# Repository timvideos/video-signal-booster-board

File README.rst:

Video Booster Board
===================

.. image:: ./img/vsb-board.png

Overview:
---------

This repository contains a KiCad PCB project for an open hardware board design that allows to improve the quality of HDMI video signals transmitted over long cables.

Key features:
-------------

* HDMI signal preconditioning with a pair of `PTN3363 <https://www.nxp.com/docs/en/data-sheet/PTN3363.pdf>`_ HDMI level shifters.
* Signal equalization controlled with on-board DIP-Switch
* On-board SiLabs `EFM32HG322F64 <https://www.silabs.com/documents/public/data-sheets/efm32hg-datasheet.pdf>`_ MCU for interactive control and board monitoring
* Supports different EDID connection scenarios

Mechanical layout and dimensions
--------------------------------

The board has been mechanically optimised for usage with the `Numato Opsis <https://hdmi2usb.tv/numato-opsis/>`_ open video capture device.
It is possible to use it with different platforms using HDMI extender cables.

.. image:: ./img/layout.png

It follows the data flow diagram presented below:

.. image:: ./img/vsb-data-flow.svg

Getting Started
---------------

Please refer to KiCad schematic files for more information regarding hardware functionalities implemented in the design.
The PCB layout has been defined with a 4-layer stackup.
Please check the geometry of differential traces implemented in the design with stackup offered by PCB vendor for optimal impedance match of HDMI traces.
There is a BOM document generated from the schematics and shared in this repository.
Please short the ``J5,J7,J8,J12`` solder jumpers on the bottom side of the PCB.
This will relay the EDID signals on both HDMI channels from input to output.
Short the ``J11,J4`` jumpers if you plan to experiment with the provided example MCU firmware.
This will make the on-board MCU accessible on EDID bus driven from ``J2`` HDMI input connector.
Please check the schematics and software codebase for any other jumper configuration.

Example firmware
----------------

The EFM32 MCU used in the design comes with a factory programmed ``AN0042`` bootloader.
In order to  make the MCU compatible with the provided example firmware it is advisable to replace the default bootloader with `Toboot <https://github.com/im-tomu/toboot>`_
over SWD interface using `OpenOCD <http://openocd.org/>`_.
The SWD signals from the MCU are exposed on test pads marked with ``IO`` and ``CLK`` on the bottom side of the Video Booster Board.
Additionally there are test pads with system ground and power supply exposed next to them.

To upload the ``Toboot`` bootloader, please follow this `instruction <https://github.com/im-tomu/toboot/tree/master/openocd>`_.
Be aware that the provided flashing instruction was originally created for a different hardware platform so the SWD connection wiring differs a little.

There is an ``example-firmware`` folder included in this repository, which contains a sample firmware driven by the RTOS derived from the `Zephyr project <https://www.zephyrproject.org/>`_.
The firmware makes the on-board EFM32 MCU act as an EDID slave for the transmitting device.

In order to build the example firmware please use the following commands::

     git clone https://github.com/antmicro/video-signal-booster-board
     cd video-signal-booster-board
     git submodule update --init --recursive
     cd example-firmware
     python3 -m pip install -r zephyr/scripts/requirements.txt
     wget https://github.com/zephyrproject-rtos/sdk-ng/releases/download/v0.10.3/zephyr-sdk-0.10.3-setup.run
     chmod +x zephyr-sdk-0.10.3-setup.run
     ./zephyr-sdk-0.10.3-setup.run -- -d <zephyr_installation_path>
     export ZEPHYR_TOOLCHAIN_VARIANT=zephyr
     export ZEPHYR_SDK_INSTALL_DIR=<zephyr_installation_path>
     source zephyr/zephyr-env.sh
     west init -l zephyr
     west update
     make

Once the firmware is compiled, connect the micro USB cable to the Video Booster Board and upload the firmware using the following command::

     dfu-util -d 1209:70b1 -D build/zephyr/zephyr.bin

Please note that in this setup the firmware doesn't stick permanently. After a power cycle a bootloader will start again. This simplifies the developing process.

The example firmware makes the MCU on Video Booster Board accessible on I2C/EDID bus slave device under the address of ``0x3a`` (7-bit notation).
It's possible to test the I2C/EDID communication by connecting an I2C master device to TX source HDMI connector (``J2``).
The example firmware makes MCU offer a single 8-bit configuration register.
Two least significant bits of this register control the states of the ``TX_EQ0`` and ``TX_EQ1`` signals that define the equalization settings of ``U3`` HDMI level shifter.
The states of those signals are also displayed on ``D8`` ``D9`` LEDs installed on board.

A sample Python code that would drive the MCU over I2C bus is::

     python
     import smbus
     bus = smbus.SMBus(<i2c_bus_number>)
     bus.write_byte_data(0x3a, 0x00, 0x03)

3D-printable enclosure
----------------------

.. image:: ./img/3dprint-enclosure.png

There are also 3D-printable enclosure .stl files available in the ``3d-models`` directory.
The enclosure allows the electronics to be covered and attaches the Video Booster Board to the Numato board installed in a typical thin mini-ITX chassis.
A connector is the source, B is the sink of the RX/TX signal. 

For printing the enclosure, use slicer settings matching your used 3D printer and filament.
Setting layer thickness to a value between 0.15mm and 0.2mm is sufficient.
The image below shows proposed print orientation.

.. image:: ./img/3dprint-orientation.png

Enclosure can be assembled with the board using 3 M1.6x8 flathead bolts.

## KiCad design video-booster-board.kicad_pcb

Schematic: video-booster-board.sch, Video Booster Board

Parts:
C1, C36: C_4u7_0603; 0603-cap; MPN C1608X5R1V475M080AC
C2, C3, C7, C8, C9, C10, C11, C12, C13, C14, C15, C16, C18, C19, C20, C21, C22, C23, C24, C25, C27, C31, C32, C33, C35, C38, C39, C40: C_100n_0402_6V3; 0402-cap; MPN 0402X104K6R3CT
C4, C17, C41: C_10u_0603; 0603-cap; MPN 06036D106MAT2A
C5, C6, C26, C34, C37, C42: C_1u_0402; 0402-cap; MPN C1005X6S1A105K050BC
C28, C30: C_2u2_0402; 0402-cap; MPN C1005X5R1A225K050BC
C29: C_10n_0402; 0402-cap; MPN 04025G103ZAT2A
D1, D2, D3, D4, D5, D6, D7: BAT54-02V-V-G; SOD-523; MPN BAT54
D8, D9: LG_L29K-G2J1-24-Z; LED_0603; MPN LG L29K-G2J1-24-Z
IC1: INA180A1IDBVT; SOT-23-5; MPN INA180A1IDBVT
J1: 0473460001; USB_Micro_B_Female_0473460001; MPN 0473460001
J2, J3: CHDMI-AMSS-01-C-Vertical; MPN CHDMI-AMSX-01-X
J4, J5, J7, J8, J11, J12, J13, J14, J15, J16, J17, J18, J19, J20: solder_jumper; SolderJumper-0.6x1.4mm; MPN None
J6, J9: 685119134923_; HDMI_A_Female_685119134923; MPN 685119134923
J10: M20-9990246; PinHeader_1x2_P2.54mm; MPN M20-9990246
N1: oshw_logo; OSHW-Logo2_7.3x6mm_Copper_Mask
N2: antmicro_logo; antmicro-logo_scaled_12mm
R1, R2: R_15R_0402; 0402-res; MPN MCWR04X15R0FTL
R3, R33, R42, R43, R44, R45, R46, R47, R48, R49, R50, R51, R52, R53, R54, R55: R_49R9_0402; 0402-res; MPN CRCW040249R9FKED
R4, R16, R38, R41: R_100R_0402; 0402-res; MPN CR0402-FX-1000GLF
R5, R6, R14, R15, R19, R24, R60: R_100k_0402; 0402-res; MPN CRCW0402100KFKEDHP
R9, R10, R21, R23, R26, R29, R31, R32, R34, R35, R36, R37, R39, R40, R58, R59: R_10k_0402; 0402-res; MPN CRCW040210K0FKEDHP
R13, R17: R_12k4_0402; 0402-res; MPN ERJ2RKF1242X
R18, R20, R25, R27, R62, R64, R68: R_27k_0402; 0402-res; MPN ERJ2RKF2702X
R30: R_806k_0402; 0402-res; MPN CRCW0402806KFKED
R56: R_1R_0402; 0402-res; MPN RC0402FR-071RL
R63, R65, R69: R_4k7_0402; 0402-res; MPN ERJ2GEJ472X
R66, R67: R_330R_0402; 0402-res; MPN MCMR04X3300FTL
SW1: 1571983-5; MPN 1571983-5
TP1, TP2, TP3, TP4, TP5, TP6, TP7: TP_SMD_0_75MM; Testpoint_smd_0_75mm
U1, U3: PTN3363; QFN-32-1EP_5x5mm; MPN PTN3363
U2: TPS2110APW; TSSOP-8_W4.4mm; MPN TPS2110APW
U4: LP2985-33DBVR; SOT-753; MPN LP2985-33DBVR
U5, U7: NTS0102GT; PSON50P100X195X50-8N; MPN NTS0102GT
U6: EFM32HG322F64; TQFP-48_7x7mm; MPN EFM32HG322F64

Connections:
+3V3: C2.2, C3.2, C4.1, C5.1, C17.1, C18.2, C19.2, C30.1, C32.1, C35.1, C37.1, C40.1, C42.1, IC1.5 (VS), R3.1, R5.1, R6.1, R14.1, R15.1, R18.2, R19.1, R20.2, R21.1, R24.1, R25.2, R26.1, R27.2, R33.1, R36.1, R37.1, R42.1, R43.1, R44.1, R45.1, R46.1, R47.1, R48.1, R49.1, R50.1, R51.1, R52.1, R53.1, R54.1, R55.1, R58.1, R59.1, U1.1 (VDD), U1.18 (VDD), U3.1 (VDD), U3.18 (VDD), U4.5 (VOUT), U5.3 (VCC_A), U5.6 (OE), U6.4, U6.19, U6.22, U6.23, U6.28, U6.43, U7.3 (VCC_A), U7.6 (OE); also elsewhere on the board
+5V: C27.2, C28.1, D4.K, D5.K, D6.K, D7.K, U4.1 (VIN), U4.3 (ON/~OFF)
+5VA: C31.1, C36.1, D2.K, D3.A, D5.A, J10.1, R68.2, U2.3 (VSNS), U2.8 (IN1)
/ADC4: R64.1, R65.2, U6.24
/ADC5: R62.1, R63.2, U6.25
/ADC6: IC1.1 (OUT), U6.26
/ADC7: R68.1, R69.2, U6.27
/C_RX_IN_CLK_N: C25.1, U1.25 (IN_D1-)
/C_RX_IN_CLK_P: C21.1, U1.26 (IN_D1+)
/C_RX_IN_D0_N: C24.1, U1.27 (IN_D2-)
/C_RX_IN_D0_P: C20.1, U1.28 (IN_D2+)
/C_RX_IN_D1_N: C23.1, U1.29 (IN_D3-)
/C_RX_IN_D1_P: C8.1, U1.30 (IN_D3+)
/C_RX_IN_D2_N: C22.1, U1.31 (IN_D4-)
/C_RX_IN_D2_P: C7.1, U1.32 (IN_D4+)
/C_TX_IN_CLK_N: C9.1, U3.31 (IN_D4-)
/C_TX_IN_CLK_P: C13.1, U3.32 (IN_D4+)
/C_TX_IN_D0_N: C10.1, U3.29 (IN_D3-)
/C_TX_IN_D0_P: C14.1, U3.30 (IN_D3+)
/C_TX_IN_D1_N: C11.1, U3.27 (IN_D2-)
/C_TX_IN_D1_P: C15.1, U3.28 (IN_D2+)
/C_TX_IN_D2_N: C12.1, U3.25 (IN_D1-)
/C_TX_IN_D2_P: C16.1, U3.26 (IN_D1+)
/DBG_LED_RX: R66.1, U6.20; also elsewhere on the board
/DBG_LED_TX: R67.1, U6.21; also elsewhere on the board
/DBG_SWCLK: U6.37; also elsewhere on the board
/DBG_SWDIO: U6.38; also elsewhere on the board
/PWR_CTL_D0: U2.1 (D0), U6.45
/PWR_CTL_D1: R60.1, U2.2 (D1), U6.46
/RX_DCC_EN: R24.2, U1.22 (DCC_EN)
/RX_DDET: R26.2, U1.3 (DDET), U6.17
/RX_EQ0: R14.2, R39.1, SW1.2.1, U1.8 (EQ0)
/RX_EQ0_R: R39.2, U6.11
/RX_EQ1: R15.2, R40.1, SW1.1.1, U1.2 (EQ1)
/RX_EQ1_R: R40.2, U6.12
/RX_HIZ_EN: R29.1, U1.24 (HIZ_EN), U6.13
/RX_HPD: J3.19, J9.19, U1.21 (HPD_SINK)
/RX_HPD_3V: U1.5 (HPD_SRC), U6.10
/RX_IN_CLK_N: C25.2, J9.12, R48.2
/RX_IN_CLK_P: C21.2, J9.10, R49.2
/RX_IN_D0_N: C24.2, J9.9, R50.2
/RX_IN_D0_P: C20.2, J9.7, R51.2
/RX_IN_D1_N: C23.2, J9.6, R52.2
/RX_IN_D1_P: C8.2, J9.4, R53.2
/RX_IN_D2_N: C22.2, J9.3, R54.2
/RX_IN_D2_P: C7.2, J9.1, R55.2
/RX_OUT_CLK_N: J3.12, U1.16 (OUT_D-)
/RX_OUT_CLK_P: J3.10, U1.15 (OUT_D1+)
/RX_OUT_D0_N: J3.9, U1.14 (OUT_D2-)
/RX_OUT_D0_P: J3.7, U1.13 (OUT_D2+)
/RX_OUT_D1_N: J3.6, U1.12 (OUT_D3-)
/RX_OUT_D1_P: J3.4, U1.11 (OUT_D3+)
/RX_OUT_D2_N: J3.3, U1.10 (OUT_D4-)
/RX_OUT_D2_P: J3.1, U1.9 (OUT_D4+)
/RX_SINK_5V: C39.2, D1.K, D3.K, J3.18, U7.7 (VCC_B)
/RX_SINK_CEC: J13.2, R16.2, R20.1, U6.42
/RX_SINK_SCL: J3.15, U7.8 (B1)
/RX_SINK_SCL_3V: J12.1, J17.2, U7.5 (A1)
/RX_SINK_SCL_MCU_3V: J17.1, U6.9
/RX_SINK_SDA: J3.16, U7.1 (B2)
/RX_SINK_SDA_3V: J8.1, J18.2, U7.4 (A2)
/RX_SINK_SDA_MCU_3V: J18.1, U6.8
/RX_SRC_5V: D1.A, D7.A, J9.18, R31.1, R32.1, R64.2
/RX_SRC_CEC: J13.1, R27.1, R41.2, U6.41
/RX_SRC_SCL: J9.15, R32.2, U1.19 (SCL_SINK)
/RX_SRC_SCL_3V: J12.2, J19.2, R37.2, U1.7 (SCL_SRC)
/RX_SRC_SCL_MCU_3V: J19.1, U6.7
/RX_SRC_SDA: J9.16, R31.2, U1.20 (SDA_SINK)
/RX_SRC_SDA_3V: J8.2, J20.2, R36.2, U1.6 (SDA_SRC)
/RX_SRC_SDA_MCU_3V: J20.1, U6.6
/RX_UTILITY: J3.14, J9.14
/TX_DCC_EN: R19.2, U3.22 (DCC_EN)
/TX_DDET: R21.2, U3.3 (DDET), U6.3
/TX_EQ0: R5.2, R9.1, SW1.4.1, U3.8 (EQ0)
/TX_EQ0_R: R9.2, U6.14
/TX_EQ1: R6.2, R10.1, SW1.3.1, U3.2 (EQ1)
/TX_EQ1_R: R10.2, U6.15
/TX_HIZ_EN: R23.1, U3.24 (HIZ_EN), U6.30
/TX_HPD: J2.19, J6.19, U3.21 (HPD_SINK)
/TX_HPD_3V: U3.5 (HPD_SRC), U6.31
/TX_IN_CLK_N: C9.2, J2.12, R47.2
/TX_IN_CLK_P: C13.2, J2.10, R46.2
/TX_IN_D0_N: C10.2, J2.9, R45.2
/TX_IN_D0_P: C14.2, J2.7, R44.2
/TX_IN_D1_N: C11.2, J2.6, R43.2
/TX_IN_D1_P: C15.2, J2.4, R42.2
/TX_IN_D2_N: C12.2, J2.3, R33.2
/TX_IN_D2_P: C16.2, J2.1, R3.2
/TX_OUT_CLK_N: J6.12, U3.10 (OUT_D4-)
/TX_OUT_CLK_P: J6.10, U3.9 (OUT_D4+)
/TX_OUT_D0_N: J6.9, U3.12 (OUT_D3-)
/TX_OUT_D0_P: J6.7, U3.11 (OUT_D3+)
/TX_OUT_D1_N: J6.6, U3.14 (OUT_D2-)
/TX_OUT_D1_P: J6.4, U3.13 (OUT_D2+)
/TX_OUT_D2_N: J6.3, U3.16 (OUT_D-)
/TX_OUT_D2_P: J6.1, U3.15 (OUT_D1+)
/TX_SINK_5V: C41.1, IC1.4 (IN-), J6.18, R34.1, R35.1, R56.2, R62.2
/TX_SINK_CEC: J14.2, R25.1, R38.2, U6.40
/TX_SINK_PWR: C34.1, IC1.3 (IN+), R56.1, U2.7 (OUT)
/TX_SINK_SCL: J6.15, R35.2, U3.19 (SCL_SINK)
/TX_SINK_SCL_3V: J7.1, J11.2, R59.2, U3.7 (SCL_SRC)
/TX_SINK_SCL_MCU_3V: J11.1, U6.48
/TX_SINK_SDA: J6.16, R34.2, U3.20 (SDA_SINK)
/TX_SINK_SDA_3V: J4.2, J5.1, R58.2, U3.6 (SDA_SRC)
/TX_SINK_SDA_MCU_3V: J4.1, U6.47
/TX_SRC_5V: C33.2, C38.2, D6.A, J2.18, U2.6 (IN2), U5.7 (VCC_B)
/TX_SRC_CEC: J14.1, R4.2, R18.1, U6.39
/TX_SRC_SCL: J2.15, U5.8 (B1)
/TX_SRC_SCL_3V: J7.2, J16.2, U5.5 (A1)
/TX_SRC_SCL_MCU_3V: J16.1, U6.2
/TX_SRC_SDA: J2.16, U5.1 (B2)
/TX_SRC_SDA_3V: J5.2, J15.2, U5.4 (A2)
/TX_SRC_SDA_MCU_3V: J15.1, U6.1
/TX_UTILITY: J2.14, J6.14
/UDN: J1.2, R1.1
/UDP: J1.3, R2.1
/VUSB: C1.1, D4.A, J1.1, U6.33
GND: C1.2, C2.1, C3.1, C4.2, C5.2, C6.2, C17.2, C18.1, C19.1, C26.2, C27.1, C28.2, C29.2, C30.2, C31.2, C32.2, C33.1, C34.2, C35.2, C36.2, C37.2, C38.1, C39.1, C40.2, C41.2, C42.2, D2.A, D8.2, D9.2, IC1.2 (GND), J1.5, J1.SH, J2.2, J2.5, J2.8, J2.11, J2.17, J2.SH, J3.2, J3.5, J3.8, J3.11, J3.17, J3.SH, J6.2, J6.5, J6.8, J6.11, J6.17, J6.SH, J9.2, J9.5, J9.8, J9.11, J9.17, J9.SH, J10.2, R13.1, R17.1, R23.2, R29.2, R30.2, R60.2, R63.1, R65.1, R69.1, SW1.1.2, SW1.2.2, SW1.3.2, SW1.4.2, U1.17 (OE_N), U1.33 (VSS), U2.5 (GND), U3.17 (OE_N), U3.33 (VSS), U4.2 (GND), U5.2 (GND), U6.5, U6.18, U6.44, U7.2 (GND); also elsewhere on the board
unnamed: C6.1, U6.29
unnamed: C26.1, U6.34
unnamed: C29.1, U4.4 (BYP)
unnamed: D8.1, R66.2
unnamed: D9.1, R67.2
unnamed: J2.13, R4.1
unnamed: J3.13, R16.1
unnamed: J6.13, R38.1
unnamed: J9.13, R41.1
unnamed: R1.2, U6.35
unnamed: R2.2, U6.36
unnamed: R13.2, U3.4 (REXT)
unnamed: R17.2, U1.4 (REXT)
unnamed: R30.1, U2.4 (ILIM)

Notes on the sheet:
SWD Debug
Opsis (RX)
Opsis (TX)
Beamer
Presenter
Config
HDMI receiver
HDMI transmitter
Power supply
MCU
SCL/SDA operate at 5V
Markings
+5V Auxillary
Consider changing R56 into 500mOhm
EDID configuration

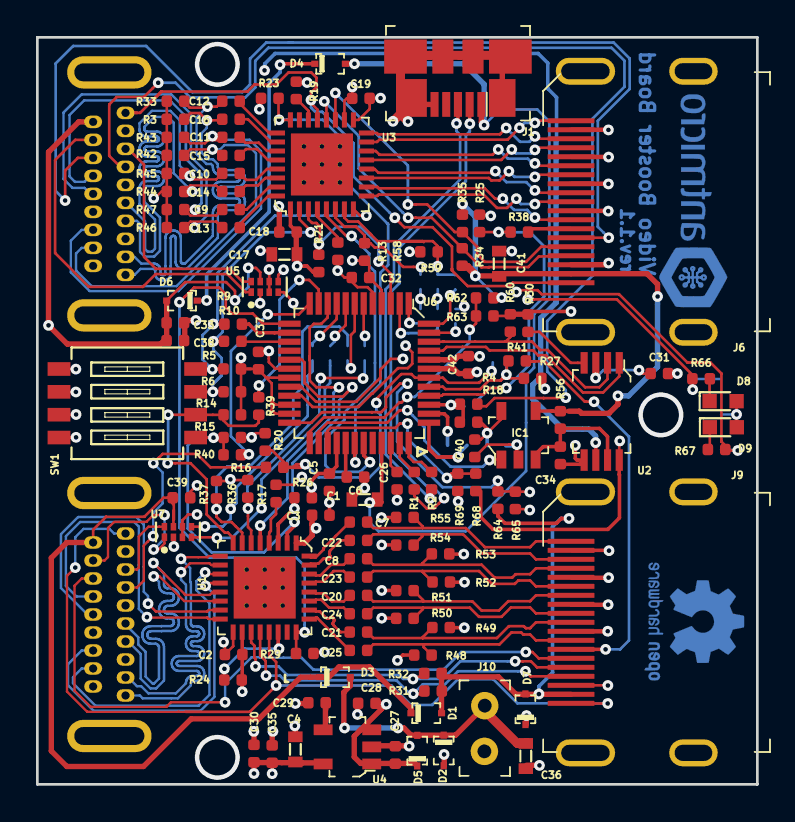
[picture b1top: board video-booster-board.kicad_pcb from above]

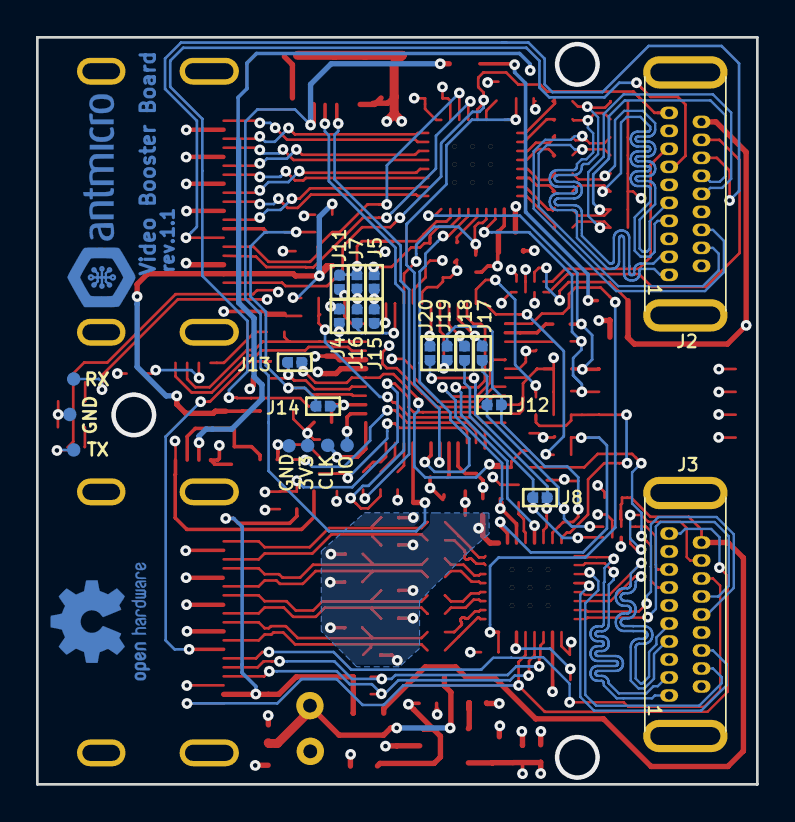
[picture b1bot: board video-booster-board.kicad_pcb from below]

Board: 4 copper layers, 40.0 x 41.5 mm, 150 parts (25 on the bottom side), 132 nets.

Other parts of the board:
3V3: TP_SMD_0_75MM; Testpoint_smd_0_75mm
CLK: TP_SMD_0_75MM; Testpoint_smd_0_75mm
GND: TP_SMD_0_75MM; Testpoint_smd_0_75mm
GND#2: TP_SMD_0_75MM; Testpoint_smd_0_75mm
IO: TP_SMD_0_75MM; Testpoint_smd_0_75mm
RX: TP_SMD_0_75MM; Testpoint_smd_0_75mm
TX: TP_SMD_0_75MM; Testpoint_smd_0_75mm

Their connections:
+3V3: 3V3.1; also elsewhere on the board
/DBG_LED_RX: RX.1; also elsewhere on the board
/DBG_LED_TX: TX.1; also elsewhere on the board
/DBG_SWCLK: CLK.1; also elsewhere on the board
/DBG_SWDIO: IO.1; also elsewhere on the board
GND: GND.1, GND#2.1; also elsewhere on the board

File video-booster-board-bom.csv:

"Id";"Designator";"Package";"Quantity";"Designation";"Supplier and ref";
1;"J9,J6";"HDMI_A_Female_685119134923";2;"685119134923_";;;
2;"R68,R20,R64,R62,R25,R27,R18";"0402-res";7;"R_27k_0402";;;
3;"J12,J5,J14,J13,J8,J7";"SolderJumper-0.6x1.4mm";6;"solder_jumper";;;
4;"J3,J2";"CHDMI-AMSS-01-C-Vertical-mod1";2;"CHDMI-AMSS-01-C-Vertical";;;
5;"U2";"TSSOP-8_W4.4mm";1;"TPS2110APW";;;
6;"CLK,IO,3V3,GND";"Testpoint_smd_0_75mm";4;"TP_SMD_0_75MM";;;
7;"R21,R32,R35,R59,R58,R23,R26,R29,R34,R36,R37,R39,R40,R31,R9,R10";"0402-res";16;"R_10k_0402";;;
8;"C27,C32,C40,C39,C38,C31,C33,C35,C2,C7,C8,C25,C24,C23,C22,C21,C20,C3,C12,C9,C10,C11,C19,C18,C16,C15,C14,C13";"0402-cap";28;"C_100n_0402_6V3";;;
9;"U6";"TQFP-48_7x7mm";1;"EFM32HG322F64";;;
10;"C5,C42,C34,C37,C26,C6";"0402-cap";6;"C_1u_0402";;;
11;"U3,U1";"QFN-32-1EP_5x5mm";2;"PTN3363";;;
12;"SW1";"1571983-5";1;"1571983-5";;;
13;"N2";"antmicro-logo_scaled_12mm";1;"antmicro_logo";;;
14;"N1";"OSHW-Logo2_7.3x6mm_Copper_Mask";1;"oshw_logo";;;
15;"C41,C4,C17";"0603-cap";3;"C_10u_0603";;;
16;"C30,C28";"0402-cap";2;"C_2u2_0402";;;
17;"R63,R69,R65";"0402-res";3;"R_4k7_0402";;;
18;"R60,R24,R5,R6,R14,R15,R19";"0402-res";7;"R_100k_0402";;;
19;"J10";"PinHeader_1x2_P2.54mm";1;"M20-9990246";;;
20;"D6,D5,D4,D3,D2,D1,D7";"SOD-523";7;"BAT54-02V-V-G";;;
21;"U7,U5";"PSON50P100X195X50-8N";2;"NTS0102GT";;;
22;"R67,R66";"0402-res";2;"R_330R_0402";;;
23;"IC1";"SOT-23-5";1;"INA180A1IDBVT";;;
24;"D9,D8";"LED_0603";2;"LG_L29K-G2J1-24-Z";;;
25;"C36,C1";"0603-cap";2;"C_4u7_0603";;;
26;"R56";"0402-res";1;"R_1R_0402";;;
27;"R54,R51,R55,R43,R53,R52,R50,R49,R48,R47,R46,R44,R45,R3,R42,R33";"0402-res";16;"R_49R9_0402";;;
28;"R30";"0402-res";1;"R_806k_0402";;;
29;"R38,R41,R4,R16";"0402-res";4;"R_100R_0402";;;
30;"C29";"0402-cap";1;"C_10n_0402";;;
31;"R13,R17";"0402-res";2;"R_12k4_0402";;;
32;"R2,R1";"0402-res";2;"R_15R_0402";;;
33;"U4";"SOT-753";1;"LP2985-33DBVR";;;
34;"J1";"USB_Micro_B_Female_0473460001";1;"0473460001";;;

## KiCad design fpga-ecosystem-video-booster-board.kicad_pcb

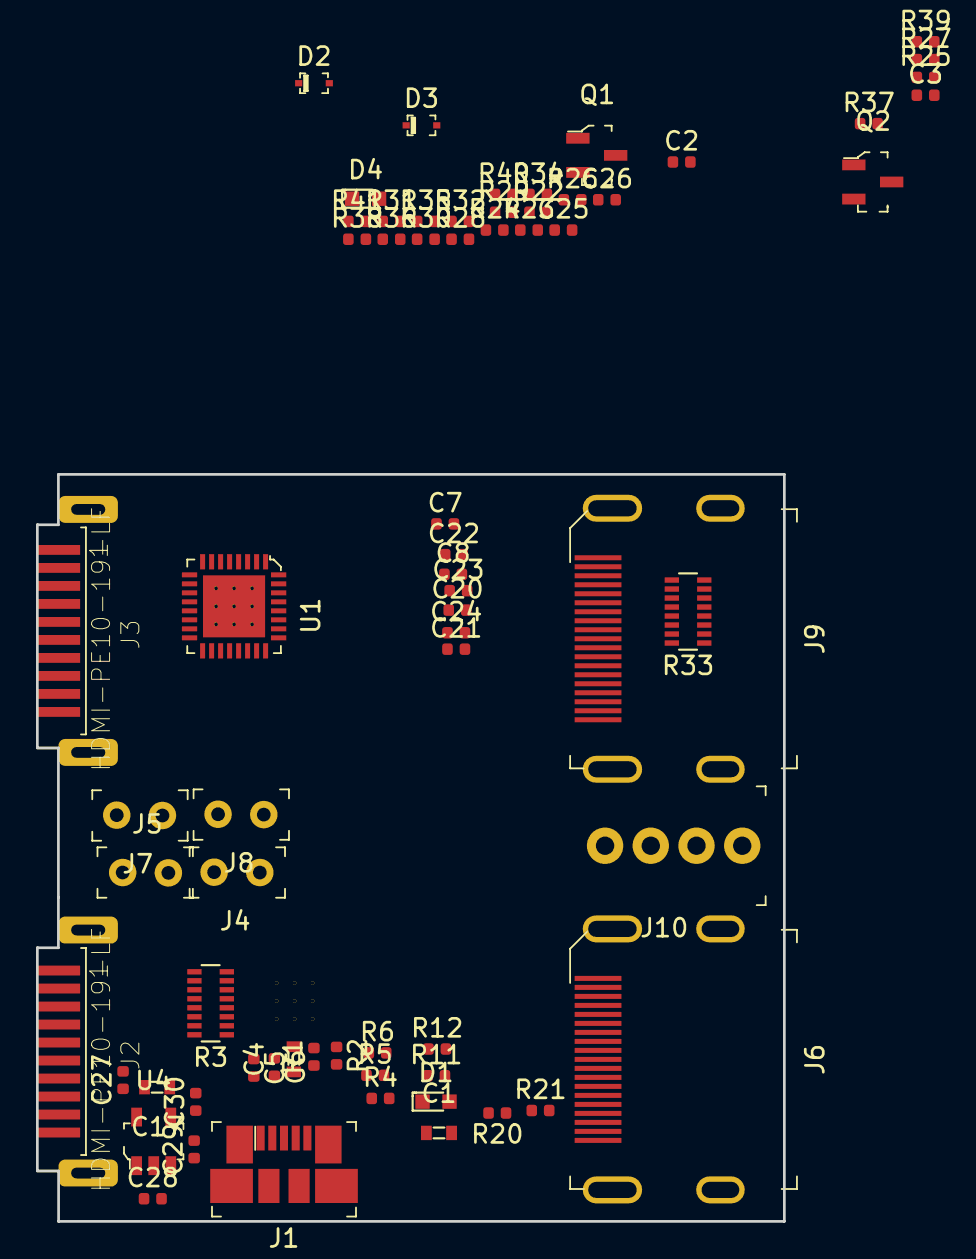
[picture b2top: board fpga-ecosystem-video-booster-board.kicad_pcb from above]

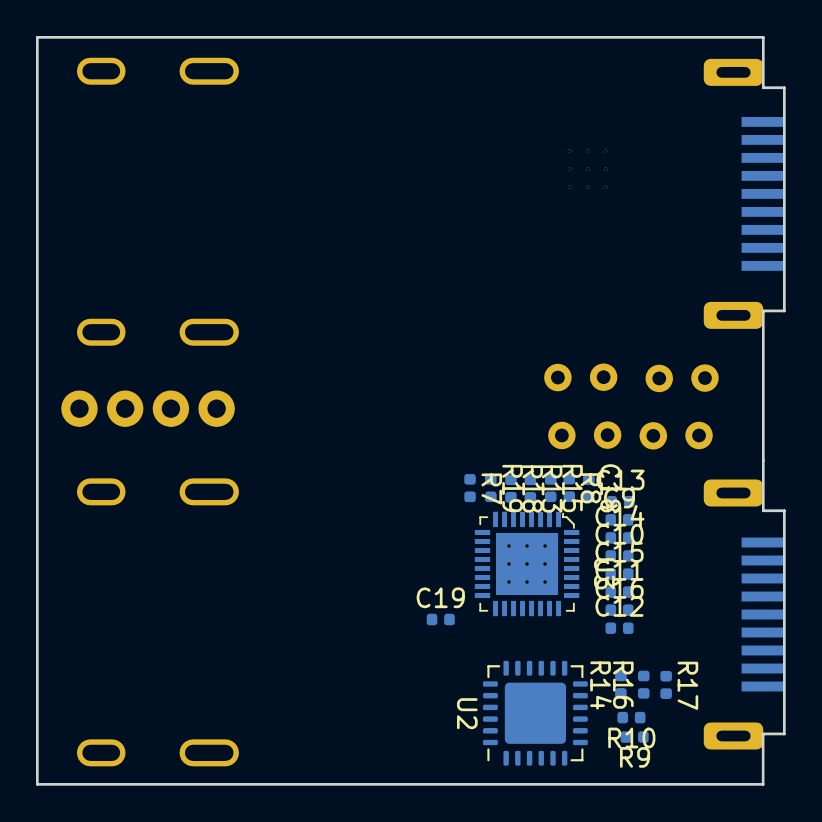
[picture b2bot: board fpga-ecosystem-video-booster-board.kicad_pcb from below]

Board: 4 copper layers, 41.5 x 41.5 mm, 91 parts (23 on the bottom side), 102 nets, no tracks yet.

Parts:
C1: C_4u7_0603; 0603-cap
C2, C3, C7, C8, C9, C10, C11, C12, C13, C14, C15, C16, C18, C19, C20, C21, C22, C23, C24, C25, C27: C_100n_0402_6V3; 0402-cap
C4, C17: C_10u_0603; 0603-cap
C5, C6, C26: C_1u_0402; 0402-cap
C28, C30: C_2u2_0402; 0402-cap
C29: C_10n_0402; 0402-cap
D1, D4: LG_L29K-G2J1-24-Z; LED_0603
D2, D3: BAT54-02V-V-G; SOD-523
J1: 0473460001; USB_Micro_B_Female_0473460001
J2, J3: HDMI-PE10-19-LF
J4, J5, J7, J8: M20-9990246; PinHeader_1x2_P2.54mm
J6, J9: 685119134923_; HDMI_A_Female_685119134923
J10: 61300411121; PinHeader_1x4_P2.54mm_Drill1.02mm
Q1, Q2: BSS138-7-F; SOT-23-3
R1, R2: R_15R_0402; 0402-res
R3, R33: 8x51R_0602_array; R_Array_Convex_8x0602
R4, R41: R_330R_0402; 0402-res
R5, R6, R14, R15, R19, R20, R24, R25: R_100k_0402; 0402-res
R7, R8, R11, R12: R_0R_0402; 0402-res
R9, R10, R16, R18, R21, R22, R23, R26, R27, R28, R29, R30, R31, R32, R34, R35, R36, R37, R38, R39, R40: R_10k_0402; 0402-res
R13, R17: R_12k4_0402; 0402-res
U1, U3: PTN3363; QFN-32-1EP_5x5mm
U2: EFM32HG309; QFN-24-1EP_5x5mm
U4: LP2985-33DBVR; SOT-753

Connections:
+5V: C27.2, C28.1, R31.1, R32.1, R34.1, R35.1, U4.1, U4.3
/C_RX_IN_CLK_N: C25.1, U1.25
/C_RX_IN_CLK_P: C21.1, U1.26
/C_RX_IN_D0_N: C24.1, U1.27
/C_RX_IN_D0_P: C20.1, U1.28
/C_RX_IN_D1_N: C23.1, U1.29
/C_RX_IN_D1_P: C8.1, U1.30
/C_RX_IN_D2_N: C22.1, U1.31
/C_RX_IN_D2_P: C7.1, U1.32
/C_TX_IN_CLK_N: C12.1, U3.25
/C_TX_IN_CLK_P: C16.1, U3.26
/C_TX_IN_D0_N: C11.1, U3.27
/C_TX_IN_D0_P: C15.1, U3.28
/C_TX_IN_D1_N: C10.1, U3.29
/C_TX_IN_D1_P: C14.1, U3.30
/C_TX_IN_D2_N: C9.1, U3.31
/C_TX_IN_D2_P: C13.1, U3.32
/DBG_SWCLK: J10.2, U2.19
/DBG_SWDIO: J10.3, U2.20
/MCU_SCL: R37.2, U1.7, U2.24, U3.7
/MCU_SDA: R36.2, U1.6, U2.23, U3.6
/RX_5V: J3.18, J9.18, Q1.1, R16.2
/RX_CEC: J3.13, J9.13
/RX_DCC_EN: R24.2, R25.1, U1.22
/RX_DDET: R26.2, U1.3
/RX_EQ0: J7.1, R14.2, R39.1, U1.8
/RX_EQ1: J8.1, R15.2, R40.1, U1.2
/RX_HIZ_EN: R28.2, R29.1, U1.24, U2.11
/RX_HPD: J3.19, J9.19
/RX_IN_CLK_N: C25.2, J9.12, R33.16
/RX_IN_CLK_P: C21.2, J9.10, R33.15
/RX_IN_D0_N: C24.2, J9.9, R33.14
/RX_IN_D0_P: C20.2, J9.7, R33.13
/RX_IN_D1_N: C23.2, J9.6, R33.12
/RX_IN_D1_P: C8.2, J9.4, R33.11
/RX_IN_D2_N: C22.2, J9.3, R33.10
/RX_IN_D2_P: C7.2, J9.1, R33.9
/RX_OUT_CLK_N: J3.12, U1.16
/RX_OUT_CLK_P: J3.10, U1.15
/RX_OUT_D0_N: J3.9, U1.14
/RX_OUT_D0_P: J3.7, U1.13
/RX_OUT_D1_N: J3.6, U1.12
/RX_OUT_D1_P: J3.4, U1.11
/RX_OUT_D2_N: J3.3, U1.10
/RX_OUT_D2_P: J3.1, U1.9
/RX_SCL: J9.15, R35.2, U1.20
/RX_SDA: J9.16, R34.2, U1.19
/RX_UTILITY: J3.14, J9.14
/TX_5V: J2.18, J6.18, Q2.1, R30.2
/TX_CEC: J2.13, J6.13
/TX_DCC_EN: R19.2, R20.1, R38.1, U3.22
/TX_DDET: R21.2, U3.3
/TX_EQ0: J4.1, R5.2, R9.1, U3.8
/TX_EQ1: J5.1, R6.2, R10.1, U3.2
/TX_HIZ_EN: R22.2, R23.1, U2.10, U3.24
/TX_HPD: J2.19, J6.19
/TX_IN_CLK_P: C16.2, J2.10, R3.15
/TX_IN_D0_N: C11.2, J2.9, R3.14
/TX_IN_D0_P: C15.2, J2.7, R3.13
/TX_IN_D1_N: C10.2, J2.6, R3.12
/TX_IN_D1_P: C14.2, J2.4, R3.11
/TX_IN_D2_N: C9.2, J2.3, R3.10
/TX_IN_D2_P: C13.2, J2.1, R3.9
/TX_OUT_CLK_N: J6.12, U3.16
/TX_OUT_CLK_P: J6.10, U3.15
/TX_OUT_D0_N: J6.9, U3.14
/TX_OUT_D0_P: J6.7, U3.13
/TX_OUT_D1_N: J6.6, U3.12
/TX_OUT_D1_P: J6.4, U3.11
/TX_OUT_D2_N: J6.3, U3.10
/TX_OUT_D2_P: J6.1, U3.9
/TX_SCL: J6.15, R8.2, R12.2, R32.2
/TX_SDA: J6.16, R7.2, R11.2, R31.2, U3.19
/TX_UTILITY: J2.14, J6.14
/VUSB: C1.1, J1.1, U2.15
GND: C1.2, C2.1, C3.1, C4.2, C5.2, C6.2, C17.2, C18.1, C19.1, C26.2, C27.1, C28.2, C29.2, C30.2, D1.2, D4.2, J1.5, J2.2, J2.5, J2.8, J2.11, J2.17, J2.SH, J3.2, J3.5, J3.8, J3.11, J3.17, J3.SH, J4.2, J5.2, J6.2, J6.5, J6.8, J6.11, J6.17, J6.SH, J7.2, J8.2, J9.2, J9.5, J9.8, J9.11, J9.17, J9.SH, J10.1, Q1.2, Q2.2, R13.1, R16.1, R17.1, R20.2, R23.2, R25.2, R29.2, R30.1, U1.33, U2.25, U3.33, U4.2
unnamed: C6.1, U2.14
unnamed: C12.2, R3.16
unnamed: C26.1, U2.16
unnamed: C29.1, U4.4
unnamed: D1.1, R4.2
unnamed: D4.1, R41.2
unnamed: J1.2, R1.1
unnamed: J1.3, R2.1
unnamed: J2.15, R7.1
unnamed: J2.16, R8.1
unnamed: J3.15, R11.1
unnamed: J3.16, R12.1
unnamed: Q1.3, R18.1, U1.17
unnamed: Q2.3, R27.1, U3.17
unnamed: R1.2, U2.17
unnamed: R2.2, U2.18
unnamed: R4.1, U2.1
unnamed: R9.2, U2.5
unnamed: R10.2, U2.6
unnamed: R13.2, U3.4
unnamed: R17.2, U1.4
unnamed: R38.2, U2.8
unnamed: R39.2, U2.3
unnamed: R40.2, U2.4
unnamed: R41.1, U2.21
VDD: C2.2, C3.2, C4.1, C5.1, C17.1, C18.2, C19.2, C30.1, J10.4, R3.1, R3.2, R3.3, R3.4, R3.5, R3.6, R3.7, R3.8, R5.1, R6.1, R14.1, R15.1, R18.2, R19.1, R21.1, R22.1, R24.1, R26.1, R27.2, R28.1, R33.1, R33.2, R33.3, R33.4, R33.5, R33.6, R33.7, R33.8, R36.1, R37.1, U1.1, U1.18, U2.2, U2.9, U2.12, U2.13, U2.22, U3.1, U3.18, U4.5

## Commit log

2019-10-23 Initial commit, dongle schematics
2019-10-23 LED and I2C input option added. Annotated sch.
2019-10-24 PCB update issues solved. PTN gnd connection fix
2019-10-24 Board shape, initial component layout
2019-10-30 Schematics with two channels. I2Cs connected directly
2019-10-30 Channels flipped for 1-side component placement
2019-10-30 New board shape, initial placement
2019-10-30 Component layout for double, one sided dongle
2019-10-30 Renamed project files
2019-10-30 Added license and basic readme
2019-10-30 Added 3D VIS to Readme
2019-10-31 Updated footprints with new 3D models
2019-11-06 Updated feature list, Added PDF schematics
2019-11-06 Schematic modified to allow EDID override, I2C switching, hot plug detect, CEC receive/transmitt
2019-11-06 Key features description added. Programming connector changed to smaller
2019-11-06 Initial placement of new components. Diff lanes routed
2019-11-06 Updated PDF schematics and 3D Vis
2019-11-13 Updated pinout proposal for a 48-pin MCU (with passthrough communication)
2019-11-13 Updated PDF schematics
2019-11-13 Removed old version of MCU
2019-11-14 I2C and CEC reconnected to pass through MCU (independent ports)
2019-11-14 Power management options added
2019-11-14 Current sensing opamp added
2019-11-15 Pinout adjustments. Placement of new components
2019-11-18 Schematic sheet changed to A2, added schematic sections
2019-11-18 Added notes to HDMI/EDID
2019-11-20 VDD replaced with +3V3
2019-11-20 CEC clamp diodes added. Open hardware logo added
2019-11-20 Local libraries generated. SCH and PCB relinked to local libraries
2019-11-20 Updated OSHW logo
2019-11-20 Cleanup, updated schematic PDF
2019-11-21 Updated 3D vis
2019-11-21 Minor changes
2019-11-22 Added pulldown on PWR_CTL_D1 and TVS protection on USB
2019-11-22 Data flow diagram added
2019-11-22 Readme formatting fix
2019-11-22 PCB routing: HDMI,control, USB
2019-11-25 Routing completed. Minor changes in control pins placement
2019-11-25 QFN-32 footprint update (larger thermal pad via size)
2019-11-25 Design Rules errors resolved
2019-11-25 Component designators arranged on PCB
2019-11-26 Differential lanes tuned
2019-11-26 Additional decoupling on MCU adn TX_SINK_5V added
2019-11-26 OSHW logo and board name added on PCB
2019-11-26 Updated sections
2019-11-26 Updated PDF
2019-11-28 Opsis side HDMI connector type changed. Board shape adjusted, DC jack added
2019-11-29 Pass-through jumpers for I2C added
2019-11-29 Pass-through jumpers for CEC added
2019-12-02 MCU type update. PCB marking update
2019-12-03 updated local project libs
2019-12-04 HDMI connector 3d model updated
2019-12-04 PDF update
2019-12-16 Updated STEP model and 3D vis
2019-12-16 Updated libs and 3D vis links in PCB file
2019-12-18 Added EFM32 getting started part
2019-12-19 Opsis side HDMI connectors changed to 90 deg
2019-12-19 Board re-routed after change
2019-12-19 Local library updated
2019-12-20 J2/J3 references corrected on F.Silk
2020-01-02 Restored plating on HDMI angular connectors
2020-01-02 Changed TX/RX side of PCB layout
2020-01-02 Routing in progress
2020-01-02 Routing II
2020-01-03 SWD changed from pinhead to testpads, routing in progress
2020-01-06 Updated layout of 3V3 LDO
2020-01-06 Removed barrel jack connector
2020-01-06 Layout almost ready
2020-01-06 Removed TVS, all signalls connected
2020-01-07 Updated designators
2020-01-07 Resolved most of DRC errors
2020-01-07 Updated bottom silkscreen
2020-01-07 Added Gerber files that validate at Eurocircuits
2020-01-07 Updated PDF schematic an 3d Vis
2020-01-08 Added BOM, schematic and gerbers for release 1.1
2020-01-08 Updated 3D Vis and README
2020-01-08 Updated .gitignore to accept BOM in CSV
2020-01-19 Added EDID configuration section
2020-01-19 Added solder jumpers for EDID configuration
2020-01-19 Updated laytout
2020-01-20 Equalized HDMI lanes, added testpads with debug uart
2020-01-21 Resolved DRC issue at Eurocircuits
2020-01-22 Add example EFM firmware
2020-01-28 Control EQ pins of video booster
2020-01-28 Set FLASH_LOAD_OFFSET for app
2020-01-28 Updated Getting Started in README
2020-01-28 Minor fix in README
2020-01-29 Renamed Images
2020-01-30 Added 3D models
2020-01-30 Updated BOM
2020-03-27 Added labeling to enclosure 3D model, added 3D printing instruction
2021-05-03 README: update formatting
2021-05-03 Update LICENSE
